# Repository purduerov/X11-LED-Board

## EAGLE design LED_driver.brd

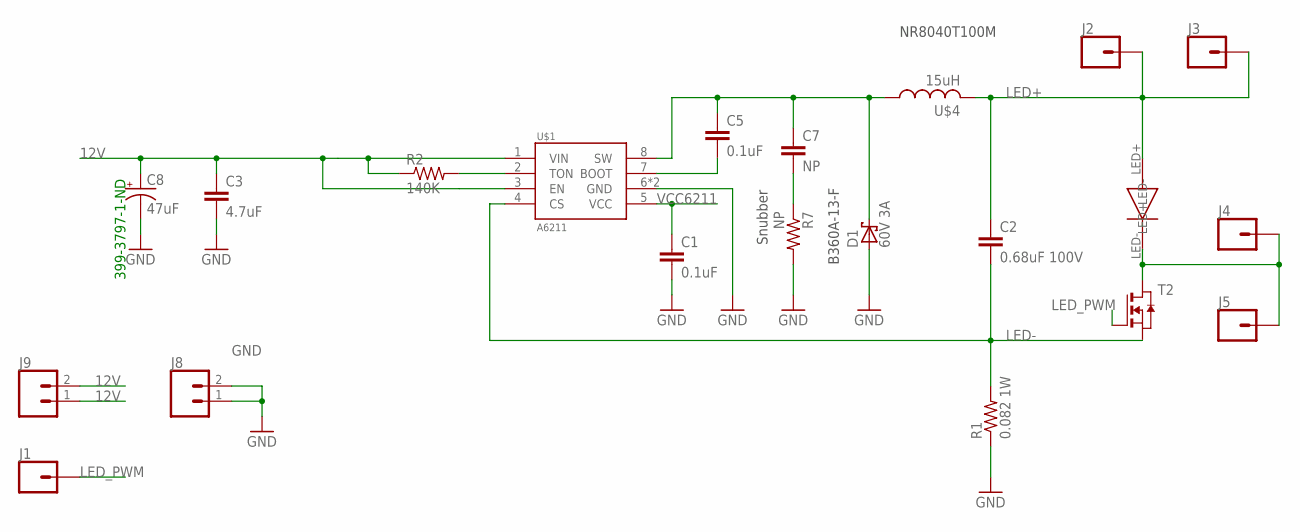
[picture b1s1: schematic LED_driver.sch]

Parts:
C1, C5: 0.1uF; C0603
C2: 0.68uF 100V; C0805
C3: 4.7uF; C0603
C7: NP; C0603
C8: 47uF; CTAN(7.30_4.30MM)
D1: 60V 3A; SMA
J1, J2, J3, J4, J5: CONN_01; 1X01
J8, J9: CONN_021X02_NO_SILK; 1X02_NO_SILK
R1: 0.082 1W; R2512
R2: 140K; R0603
R7: NP; R1206
T2: NMOSSOT23; SOT-23
U$1: A6211; SOIC8N-LJ
U$3: LED_00H53
U$4: 15uH; HCMA1305

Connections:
12V: C3.1, C8.+, J9.1, J9.2, R2.1, U$1.1 (VIN), U$1.3 (EN)
GND: C1.2, C3.2, C8.-, D1.A, J8.1, J8.2, R1.1, R7.2, U$1.6 (GND), U$1.PAD (GND)
LED+: C2.1, J2.1, J3.1, U$3.LED+, U$4.P$2 (2)
LED-: C2.2, R1.2, T2.2 (S), U$1.4 (CS)
LED_PWM: J1.1, T2.3 (G)
unnamed: R2.2, U$1.2 (TON)
unnamed: C7.2, R7.1
unnamed: J4.1, J5.1, T2.1 (D), U$3.LED-
unnamed: C5.2, U$1.7 (BOOT)
unnamed: C5.1, C7.1, D1.C, U$1.8 (SW), U$4.P$1 (1)
VCC6211: C1.1, U$1.5 (VCC)

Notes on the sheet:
NR8040T100M
B360A-13-F
Snubber
399-3797-1-ND

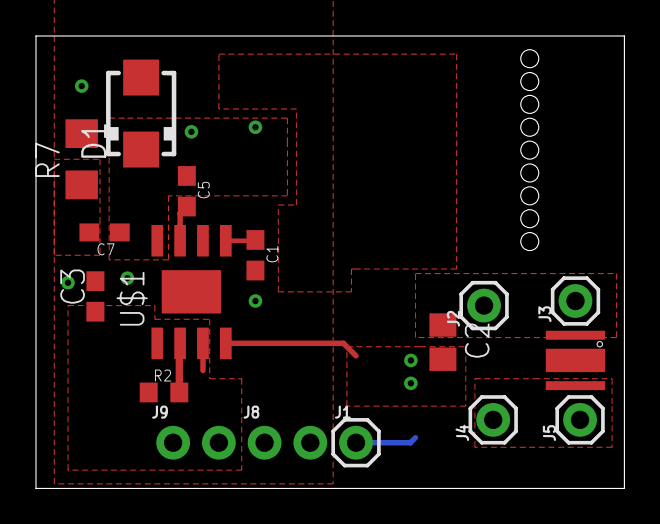
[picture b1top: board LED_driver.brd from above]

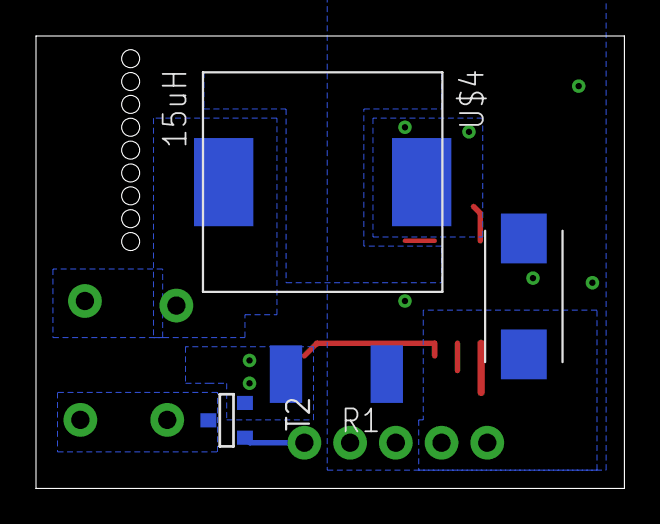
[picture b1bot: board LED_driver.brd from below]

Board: 2 copper layers, 32.7 x 25.1 mm, 21 parts (4 on the bottom side), 11 nets.

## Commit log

2018-11-19 First iteration
2018-12-01 New revision with MOSFET connected to the Enable of the IC
2018-12-06 continued revisions
2018-12-24 added 1 polygon

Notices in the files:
parts and their libraries:
SparkFun-Connectors: Licensing: Creative Commons ShareAlike 4.0 International - https://creativecommons.org/licenses/by-sa/4.0
